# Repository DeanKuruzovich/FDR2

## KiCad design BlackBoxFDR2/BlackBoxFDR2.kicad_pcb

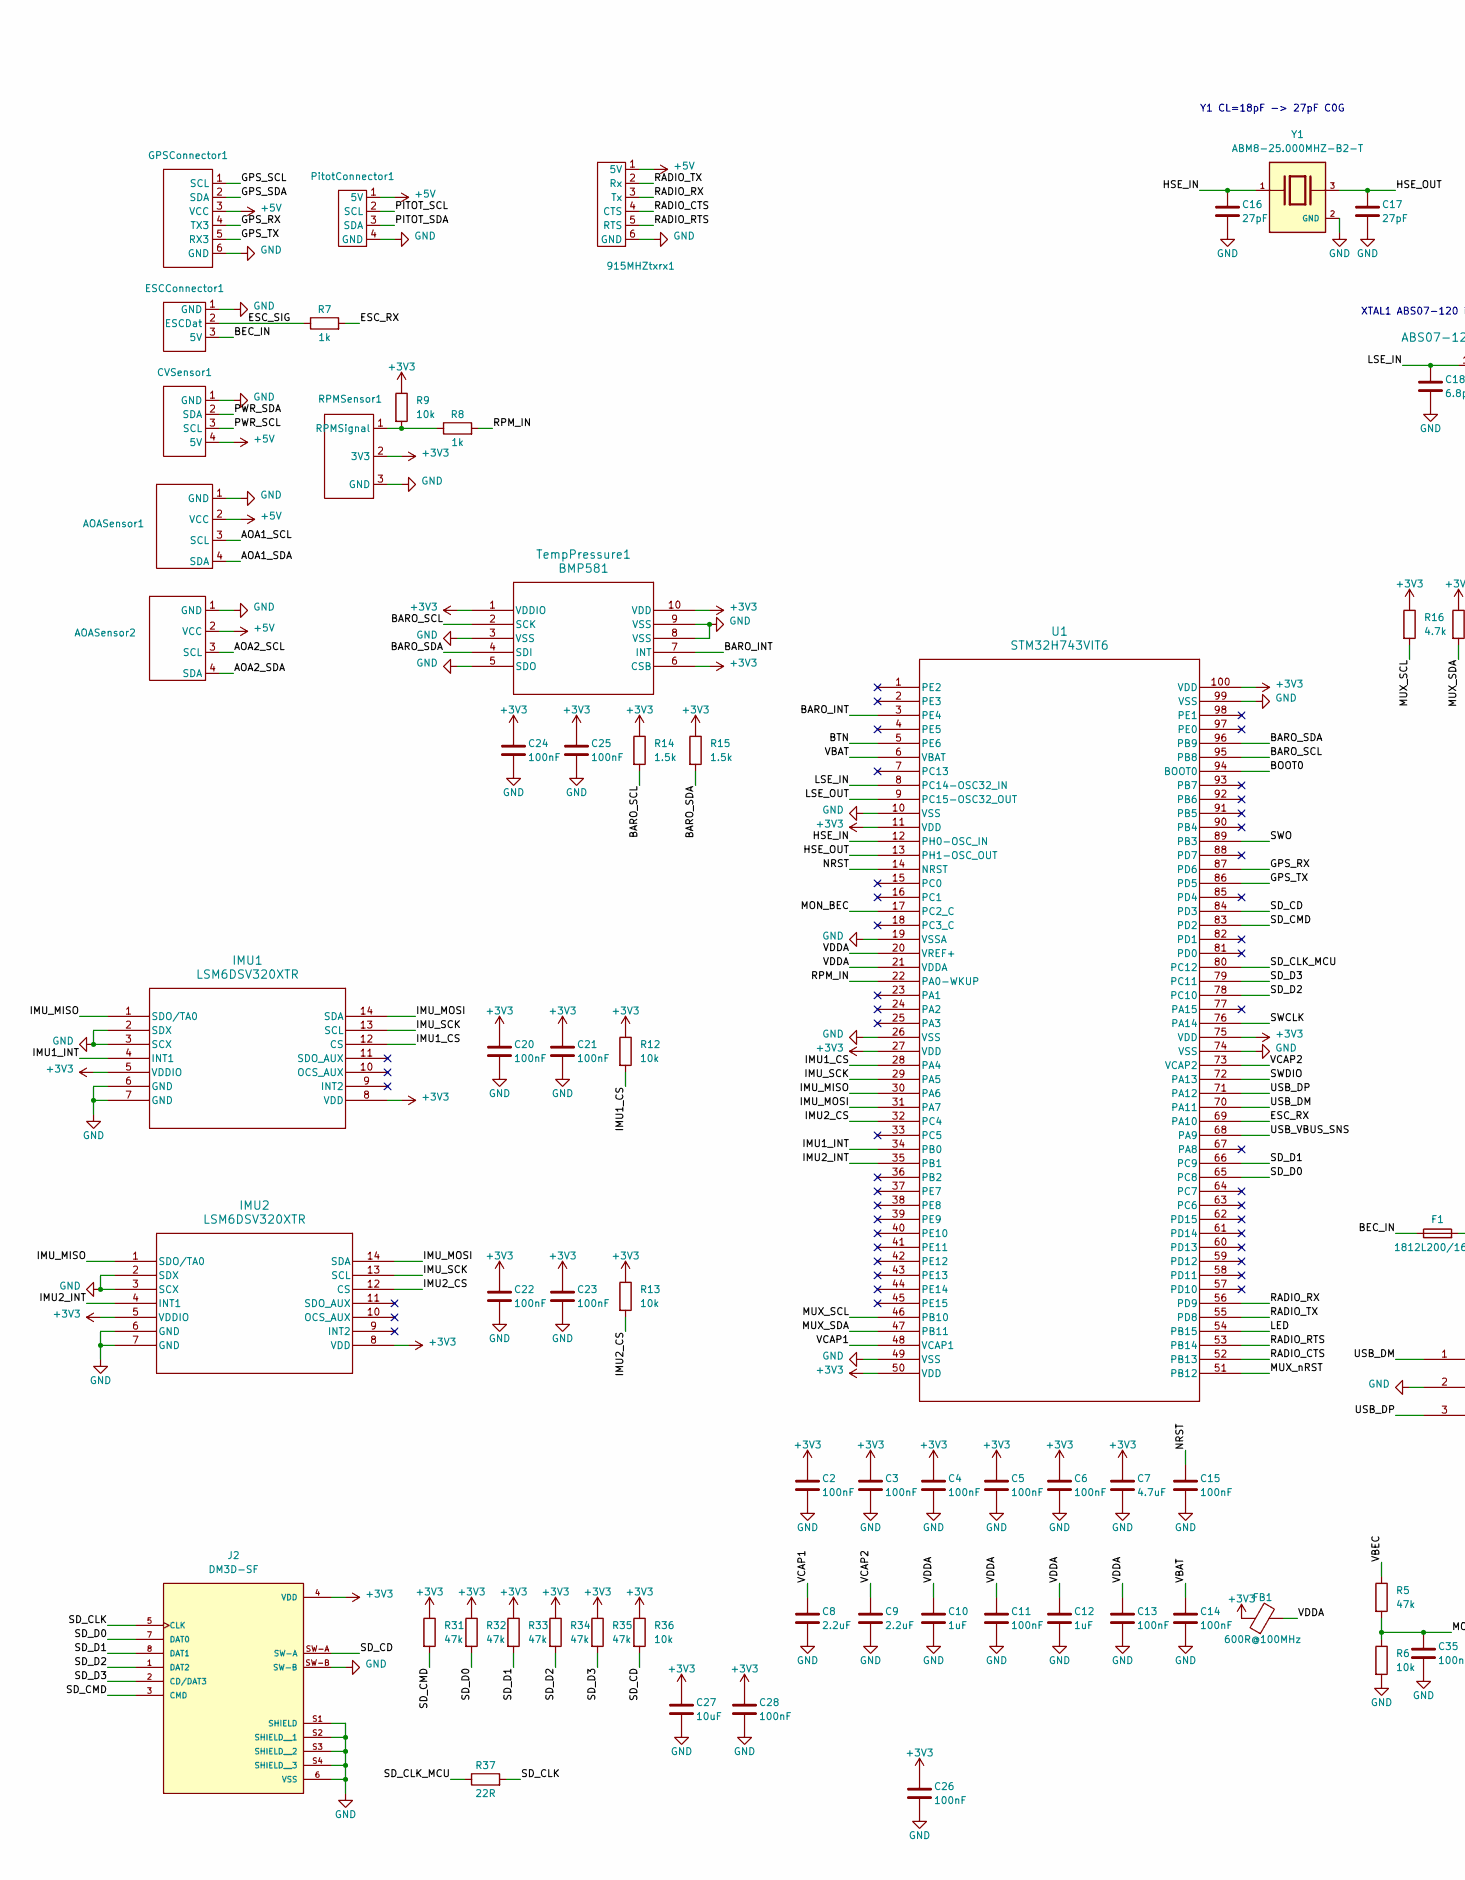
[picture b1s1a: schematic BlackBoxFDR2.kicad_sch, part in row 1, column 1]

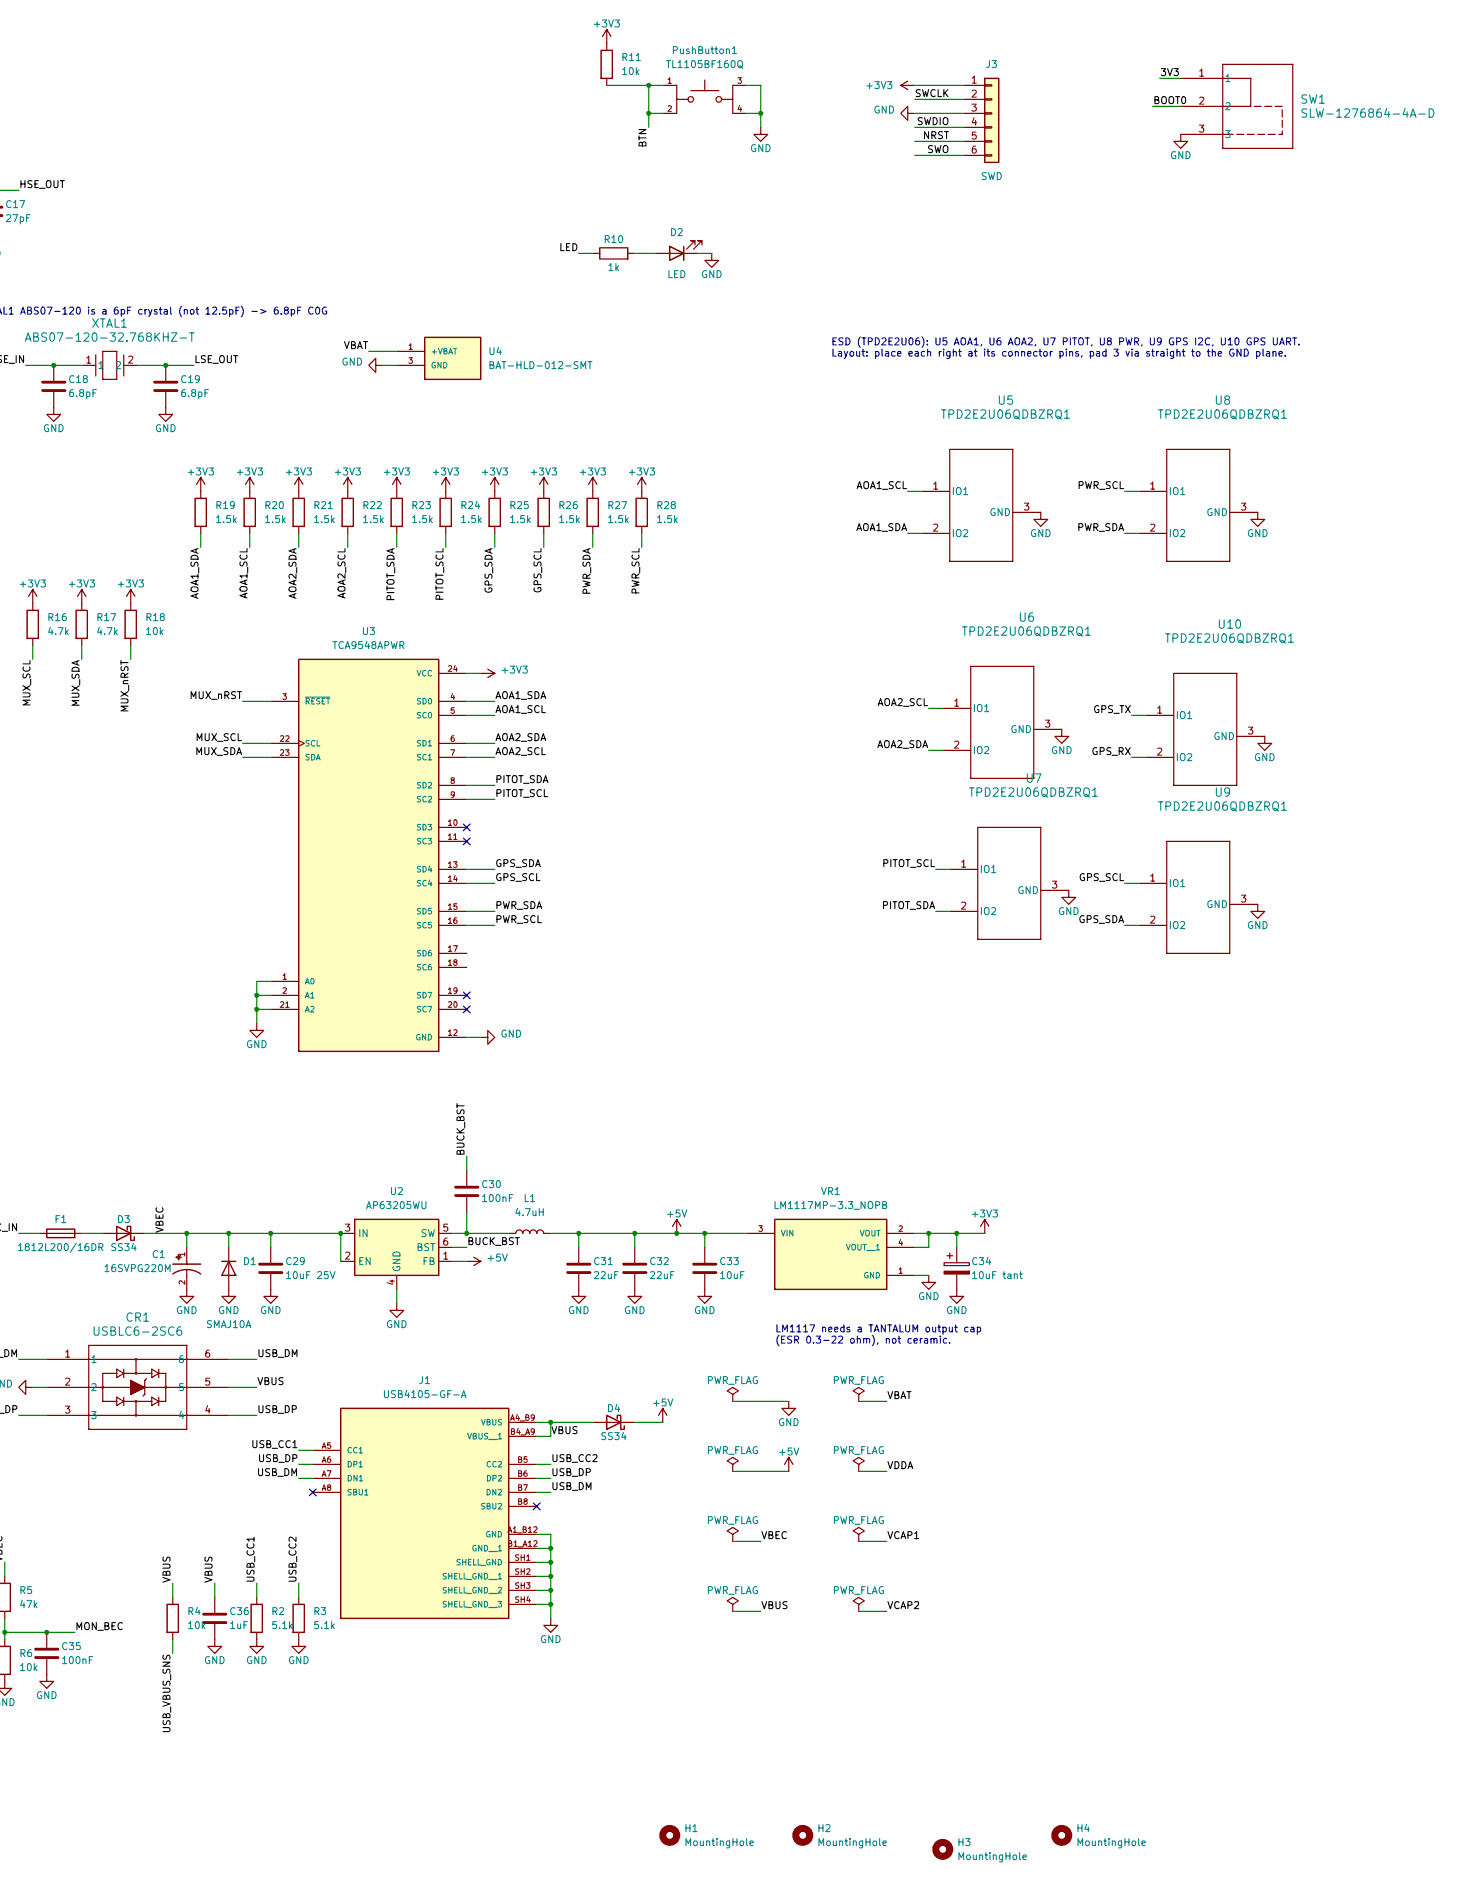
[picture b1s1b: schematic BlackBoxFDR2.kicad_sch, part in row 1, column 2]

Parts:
915MHZtxrx1: PinHeader_1x06_P2.54mm_Vertical
AOASensor1, AOASensor2: JST_EH_B4B-EH-A_1x04_P2.50mm_Vertical
C1: 16SVPG220M; CAP_16SVPG220M; PARTREV 05-Mar-21
C2, C3, C4, C5, C6, C11, C13, C14, C15, C20, C21, C22, C23, C24, C25, C26, C28, C30, C35: 100nF; C_0402_1005Metric
C7: 4.7uF; C_0603_1608Metric
C8, C9: 2.2uF; C_0402_1005Metric
C10, C12, C36: 1uF; C_0402_1005Metric
C16, C17: 27pF; C_0402_1005Metric
C18, C19: 6.8pF; C_0402_1005Metric
C27: 10uF; C_0603_1608Metric
C29: 10uF 25V; C_1206_3216Metric
C31, C32: 22uF; C_0805_2012Metric
C33: 10uF; C_0805_2012Metric
C34: 10uF tant; CP_EIA-3216-18_Kemet-A; MPN T491A106K016AT
CR1: USBLC6-2SC6; SOT23-6L_STM-M
CVSensor1: JST_EH_B4B-EH-A_1x04_P2.50mm_Vertical
D1: SMAJ10A; SMASeries_LTF-M
D2: LED; PinSocket_1x02_P2.54mm_Horizontal
D3, D4: SS34; D_SMA
ESCConnector1: escCon
F1: 1812L200/16DR; Fuse_1812_4532Metric_Pad1.30x3.40mm_HandSolder
FB1: 600R@100MHz; L_0603_1608Metric
GPSConnector1: JST_EH_B6B-EH-A_1x06_P2.50mm_Vertical
H1, H2, H3, H4: MountingHole; MountingHole_3.2mm_M3_Pad
IMU1, IMU2: LSM6DSV320XTR; LGA-14L_2p5X3X0p83_STM-M
J1: USB4105-GF-A; GCT_USB4105-GF-A; PARTREV B4
J2: DM3D-SF; HRS_DM3D-SF; PARTREV 2017.1
J3: SWD; PinHeader_1x06_P2.54mm_Vertical
L1: 4.7uH; L_Coilcraft_XAL4020-XXX; MPN XAL4020-472MEC
PitotConnector1: JST_EH_B4B-EH-A_1x04_P2.50mm_Vertical
PushButton1: TL1105BF160Q; SW_TL1105BF160Q; PARTREV A
R2, R3: 5.1k; R_0402_1005Metric
R4, R6, R9, R11, R12, R13, R18, R36: 10k; R_0402_1005Metric
R5, R31, R32, R33, R34, R35: 47k; R_0402_1005Metric
R7, R8, R10: 1k; R_0402_1005Metric
R14, R15, R19, R20, R21, R22, R23, R24, R25, R26, R27, R28: 1.5k; R_0402_1005Metric
R16, R17: 4.7k; R_0402_1005Metric
R37: 22R; R_0402_1005Metric
RPMSensor1: JST_EH_B3B-EH-A_1x03_P2.50mm_Vertical
SW1: SLW-1276864-4A-D; PinHeader_1x03_P2.54mm_Vertical
TempPressure1: BMP581; QFN10_BMP581_BOS-M
U1: STM32H743VIT6; LQFP100-14x14mm
U2: AP63205WU; TSOT-23-6
U3: TCA9548APWR; SOP65P640X120-24N; PARTREV G
U4: BAT-HLD-012-SMT; BATHLD012SMT; MOUSER_PART_NUMBER 712-BAT-HLD-012-SMT; DigiKey_Part_Number BAT-HLD-012-SMTCT-ND
U5, U6, U7, U8, U9, U10: TPD2E2U06QDBZRQ1; DBZ0003A_M
VR1: LM1117MP-3.3_NOPB; VREG_LM1117MP-3.3_NOPB; PARTREV Q
XTAL1: ABS07-120-32.768KHZ-T; XTAL_32768
Y1: ABM8-25.000MHZ-B2-T; XTAL_ABM8-25.000MHZ-B2-T; PARTREV 44041

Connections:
+3V3: C2.1, C3.1, C4.1, C5.1, C6.1, C7.1, C20.1, C21.1, C22.1, C23.1, C24.1, C25.1, C26.1, C27.1, C28.1, C34.1, FB1.1, IMU1.5 (VDDIO), IMU1.8 (VDD), IMU2.5 (VDDIO), IMU2.8 (VDD), J2.4 (VDD), J3.1, R9.1, R11.1, R12.1, R13.1, R14.1, R15.1, R16.1, R17.1, R18.1, R19.1, R20.1, R21.1, R22.1, R23.1, R24.1, R25.1, R26.1, R27.1, R28.1, R31.1, R32.1, R33.1, R34.1, R35.1, R36.1, RPMSensor1.2 (3V3), TempPressure1.1 (VDDIO), TempPressure1.6 (CSB), TempPressure1.10 (VDD), U1.11 (VDD), U1.27 (VDD), U1.50 (VDD), U1.75 (VDD), U1.100 (VDD), U3.24 (VCC), VR1.2 (VOUT), VR1.4 (VOUT__1); also elsewhere on the board
+5V: 915MHZtxrx1.1 (5V), AOASensor1.2 (VCC), AOASensor2.2 (VCC), C31.1, C32.1, C33.1, CVSensor1.4 (5V), D4.1 (K), GPSConnector1.3 (VCC), L1.2, PitotConnector1.1 (5V), U2.1 (FB), VR1.3 (VIN)
/3V3: SW1.1
/AOA1_SCL: AOASensor1.3 (SCL), R20.2, U3.5 (SC0), U5.1 (IO1)
/AOA1_SDA: AOASensor1.4 (SDA), R19.2, U3.4 (SD0), U5.2 (IO2)
/AOA2_SCL: AOASensor2.3 (SCL), R22.2, U3.7 (SC1), U6.1 (IO1)
/AOA2_SDA: AOASensor2.4 (SDA), R21.2, U3.6 (SD1), U6.2 (IO2)
/BARO_INT: TempPressure1.7 (INT), U1.3 (PE4)
/BARO_SCL: R14.2, TempPressure1.2 (SCK), U1.95 (PB8)
/BARO_SDA: R15.2, TempPressure1.4 (SDI), U1.96 (PB9)
/BEC_IN: ESCConnector1.3 (5V), F1.1
/BOOT0: SW1.2, U1.94 (BOOT0); also elsewhere on the board
/BTN: PushButton1.1, PushButton1.2, R11.2, U1.5 (PE6)
/BUCK_BST: C30.1, U2.6 (BST)
/ESC_RX: R7.2, U1.69 (PA10)
/ESC_SIG: ESCConnector1.2 (ESCDat), R7.1
/GPS_RX: GPSConnector1.4 (TX3), U1.87 (PD6), U10.2 (IO2)
/GPS_SCL: GPSConnector1.1 (SCL), R26.2, U3.14 (SC4), U9.1 (IO1)
/GPS_SDA: GPSConnector1.2 (SDA), R25.2, U3.13 (SD4), U9.2 (IO2)
/GPS_TX: GPSConnector1.5 (RX3), U1.86 (PD5), U10.1 (IO1)
/HSE_IN: C16.1, U1.12 (PH0-OSC_IN), Y1.1
/HSE_OUT: C17.1, U1.13 (PH1-OSC_OUT), Y1.3
/IMU1_CS: IMU1.12 (CS), R12.2, U1.28 (PA4)
/IMU1_INT: IMU1.4 (INT1), U1.34 (PB0)
/IMU2_CS: IMU2.12 (CS), R13.2, U1.32 (PC4)
/IMU2_INT: IMU2.4 (INT1), U1.35 (PB1)
/IMU_MISO: IMU1.1 (SDO/TA0), IMU2.1 (SDO/TA0), U1.30 (PA6)
/IMU_MOSI: IMU1.14 (SDA), IMU2.14 (SDA), U1.31 (PA7)
/IMU_SCK: IMU1.13 (SCL), IMU2.13 (SCL), U1.29 (PA5)
/LED: R10.1, U1.54 (PB15)
/LSE_IN: C18.1, U1.8 (PC14-OSC32_IN), XTAL1.1
/LSE_OUT: C19.1, U1.9 (PC15-OSC32_OUT), XTAL1.2
/MON_BEC: C35.1, R5.2, R6.1, U1.17 (PC2_C)
/MUX_SCL: R16.2, U1.46 (PB10), U3.22 (SCL)
/MUX_SDA: R17.2, U1.47 (PB11), U3.23 (SDA)
/MUX_nRST: R18.2, U1.51 (PB12), U3.3 (~RESET)
/NRST: C15.1, J3.5, U1.14 (NRST)
/PITOT_SCL: PitotConnector1.2 (SCL), R24.2, U3.9 (SC2), U7.1 (IO1)
/PITOT_SDA: PitotConnector1.3 (SDA), R23.2, U3.8 (SD2), U7.2 (IO2)
/PWR_SCL: CVSensor1.3 (SCL), R28.2, U3.16 (SC5), U8.1 (IO1)
/PWR_SDA: CVSensor1.2 (SDA), R27.2, U3.15 (SD5), U8.2 (IO2)
/RADIO_CTS: 915MHZtxrx1.4 (CTS), U1.52 (PB13)
/RADIO_RTS: 915MHZtxrx1.5 (RTS), U1.53 (PB14)
/RADIO_RX: 915MHZtxrx1.3 (Tx), U1.56 (PD9)
/RADIO_TX: 915MHZtxrx1.2 (Rx), U1.55 (PD8)
/RPM_IN: R8.2, U1.22 (PA0-WKUP)
/SD_CD: J2.SW-A, R36.2, U1.84 (PD3)
/SD_CLK: J2.5 (CLK), R37.2
/SD_CLK_MCU: R37.1, U1.80 (PC12)
/SD_CMD: J2.3 (CMD), R31.2, U1.83 (PD2)
/SD_D0: J2.7 (DAT0), R32.2, U1.65 (PC8)
/SD_D1: J2.8 (DAT1), R33.2, U1.66 (PC9)
/SD_D2: J2.1 (DAT2), R34.2, U1.78 (PC10)
/SD_D3: J2.2 (CD/DAT3), R35.2, U1.79 (PC11)
/SWCLK: J3.2, U1.76 (PA14)
/SWDIO: J3.4, U1.72 (PA13)
/SWO: J3.6, U1.89 (PB3)
/USB_CC1: J1.A5 (CC1), R2.1
/USB_CC2: J1.B5 (CC2), R3.1
/USB_DM: CR1.1, CR1.6, J1.A7 (DN1), J1.B7 (DN2), U1.70 (PA11)
/USB_DP: CR1.3, CR1.4, J1.A6 (DP1), J1.B6 (DP2), U1.71 (PA12)
/USB_VBUS_SNS: R4.2, U1.68 (PA9)
/VBAT: C14.1, U1.6 (VBAT), U4.1 (+VBAT), U4.2 (+VBAT)
/VBEC: C1.1, C29.1, D1.1 (K), D3.1 (K), R5.1, U2.2 (EN), U2.3 (IN)
/VBUS: C36.1, CR1.5, D4.2 (A), J1.A4_B9 (VBUS), J1.B4_A9 (VBUS__1), R4.1
/VCAP1: C8.1, U1.48 (VCAP1)
/VCAP2: C9.1, U1.73 (VCAP2)
/VDDA: C10.1, C11.1, C12.1, C13.1, FB1.2, U1.20 (VREF+), U1.21 (VDDA)
GND: 915MHZtxrx1.6 (GND), AOASensor1.1 (GND), AOASensor2.1 (GND), C1.2, C2.2, C3.2, C4.2, C5.2, C6.2, C7.2, C8.2, C9.2, C10.2, C11.2, C12.2, C13.2, C14.2, C15.2, C16.2, C17.2, C18.2, C19.2, C20.2, C21.2, C22.2, C23.2, C24.2, C25.2, C26.2, C27.2, C28.2, C29.2, C31.2, C32.2, C33.2, C34.2, C35.2, C36.2, CR1.2, CVSensor1.1 (GND), D1.2 (A), D2.1 (K), ESCConnector1.1 (GND), GPSConnector1.6 (GND), IMU1.2 (SDX), IMU1.3 (SCX), IMU1.6 (GND), IMU1.7 (GND), IMU2.2 (SDX), IMU2.3 (SCX), IMU2.6 (GND), IMU2.7 (GND), J1.A1_B12 (GND), J1.B1_A12 (GND__1), J1.SH1 (SHELL_GND), J1.SH2 (SHELL_GND__1), J1.SH3 (SHELL_GND__2), J1.SH4 (SHELL_GND__3), J2.6 (VSS), J2.S1 (SHIELD), J2.S2 (SHIELD__1), J2.S3 (SHIELD__2), J2.S4 (SHIELD__3), J2.SW-B, J3.3, PitotConnector1.4 (GND), PushButton1.3, PushButton1.4, R2.2, R3.2, R6.2, RPMSensor1.3 (GND), SW1.3, TempPressure1.3 (VSS), TempPressure1.5 (SDO), TempPressure1.8 (VSS), TempPressure1.9 (VSS), U1.10 (VSS), U1.19 (VSSA), U1.26 (VSS), U1.49 (VSS), U1.74 (VSS), U1.99 (VSS), U2.4 (GND), U3.1 (A0), U3.2 (A1), U3.12 (GND), U3.21 (A2), U4.3 (GND), U5.3 (GND), U6.3 (GND), U7.3 (GND), U8.3 (GND), U9.3 (GND), U10.3 (GND), VR1.1 (GND), Y1.2 (GND), Y1.4 (GND); also elsewhere on the board
unnamed: D2.2 (A), R10.2
unnamed: D3.2 (A), F1.2
unnamed: R8.1, R9.2, RPMSensor1.1 (RPMSignal)
unnamed: C30.2, L1.1, U2.5 (SW)

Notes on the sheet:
XTAL1 ABS07-120 is a 6pF crystal (not 12.5pF) -> 6.8pF C0G
LM1117 needs a TANTALUM output cap (ESR 0.3-22 ohm), not ceramic.
Y1 CL=18pF -> 27pF C0G
ESD (TPD2E2U06): U5 AOA1, U6 AOA2, U7 PITOT, U8 PWR, U9 GPS I2C, U10 GPS UART. Layout: place each right at its connector pins, pad 3 via straight to the GND plane.

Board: 4 copper layers, 114 parts (0 on the bottom side), 72 nets, no tracks yet.

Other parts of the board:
R1: 10k; R_0402_1005Metric
R29, R30: 1.5k; R_0402_1005Metric

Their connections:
+3V3: R29.1, R30.1; also elsewhere on the board
/BOOT0: R1.1; also elsewhere on the board
GND: R1.2; also elsewhere on the board
